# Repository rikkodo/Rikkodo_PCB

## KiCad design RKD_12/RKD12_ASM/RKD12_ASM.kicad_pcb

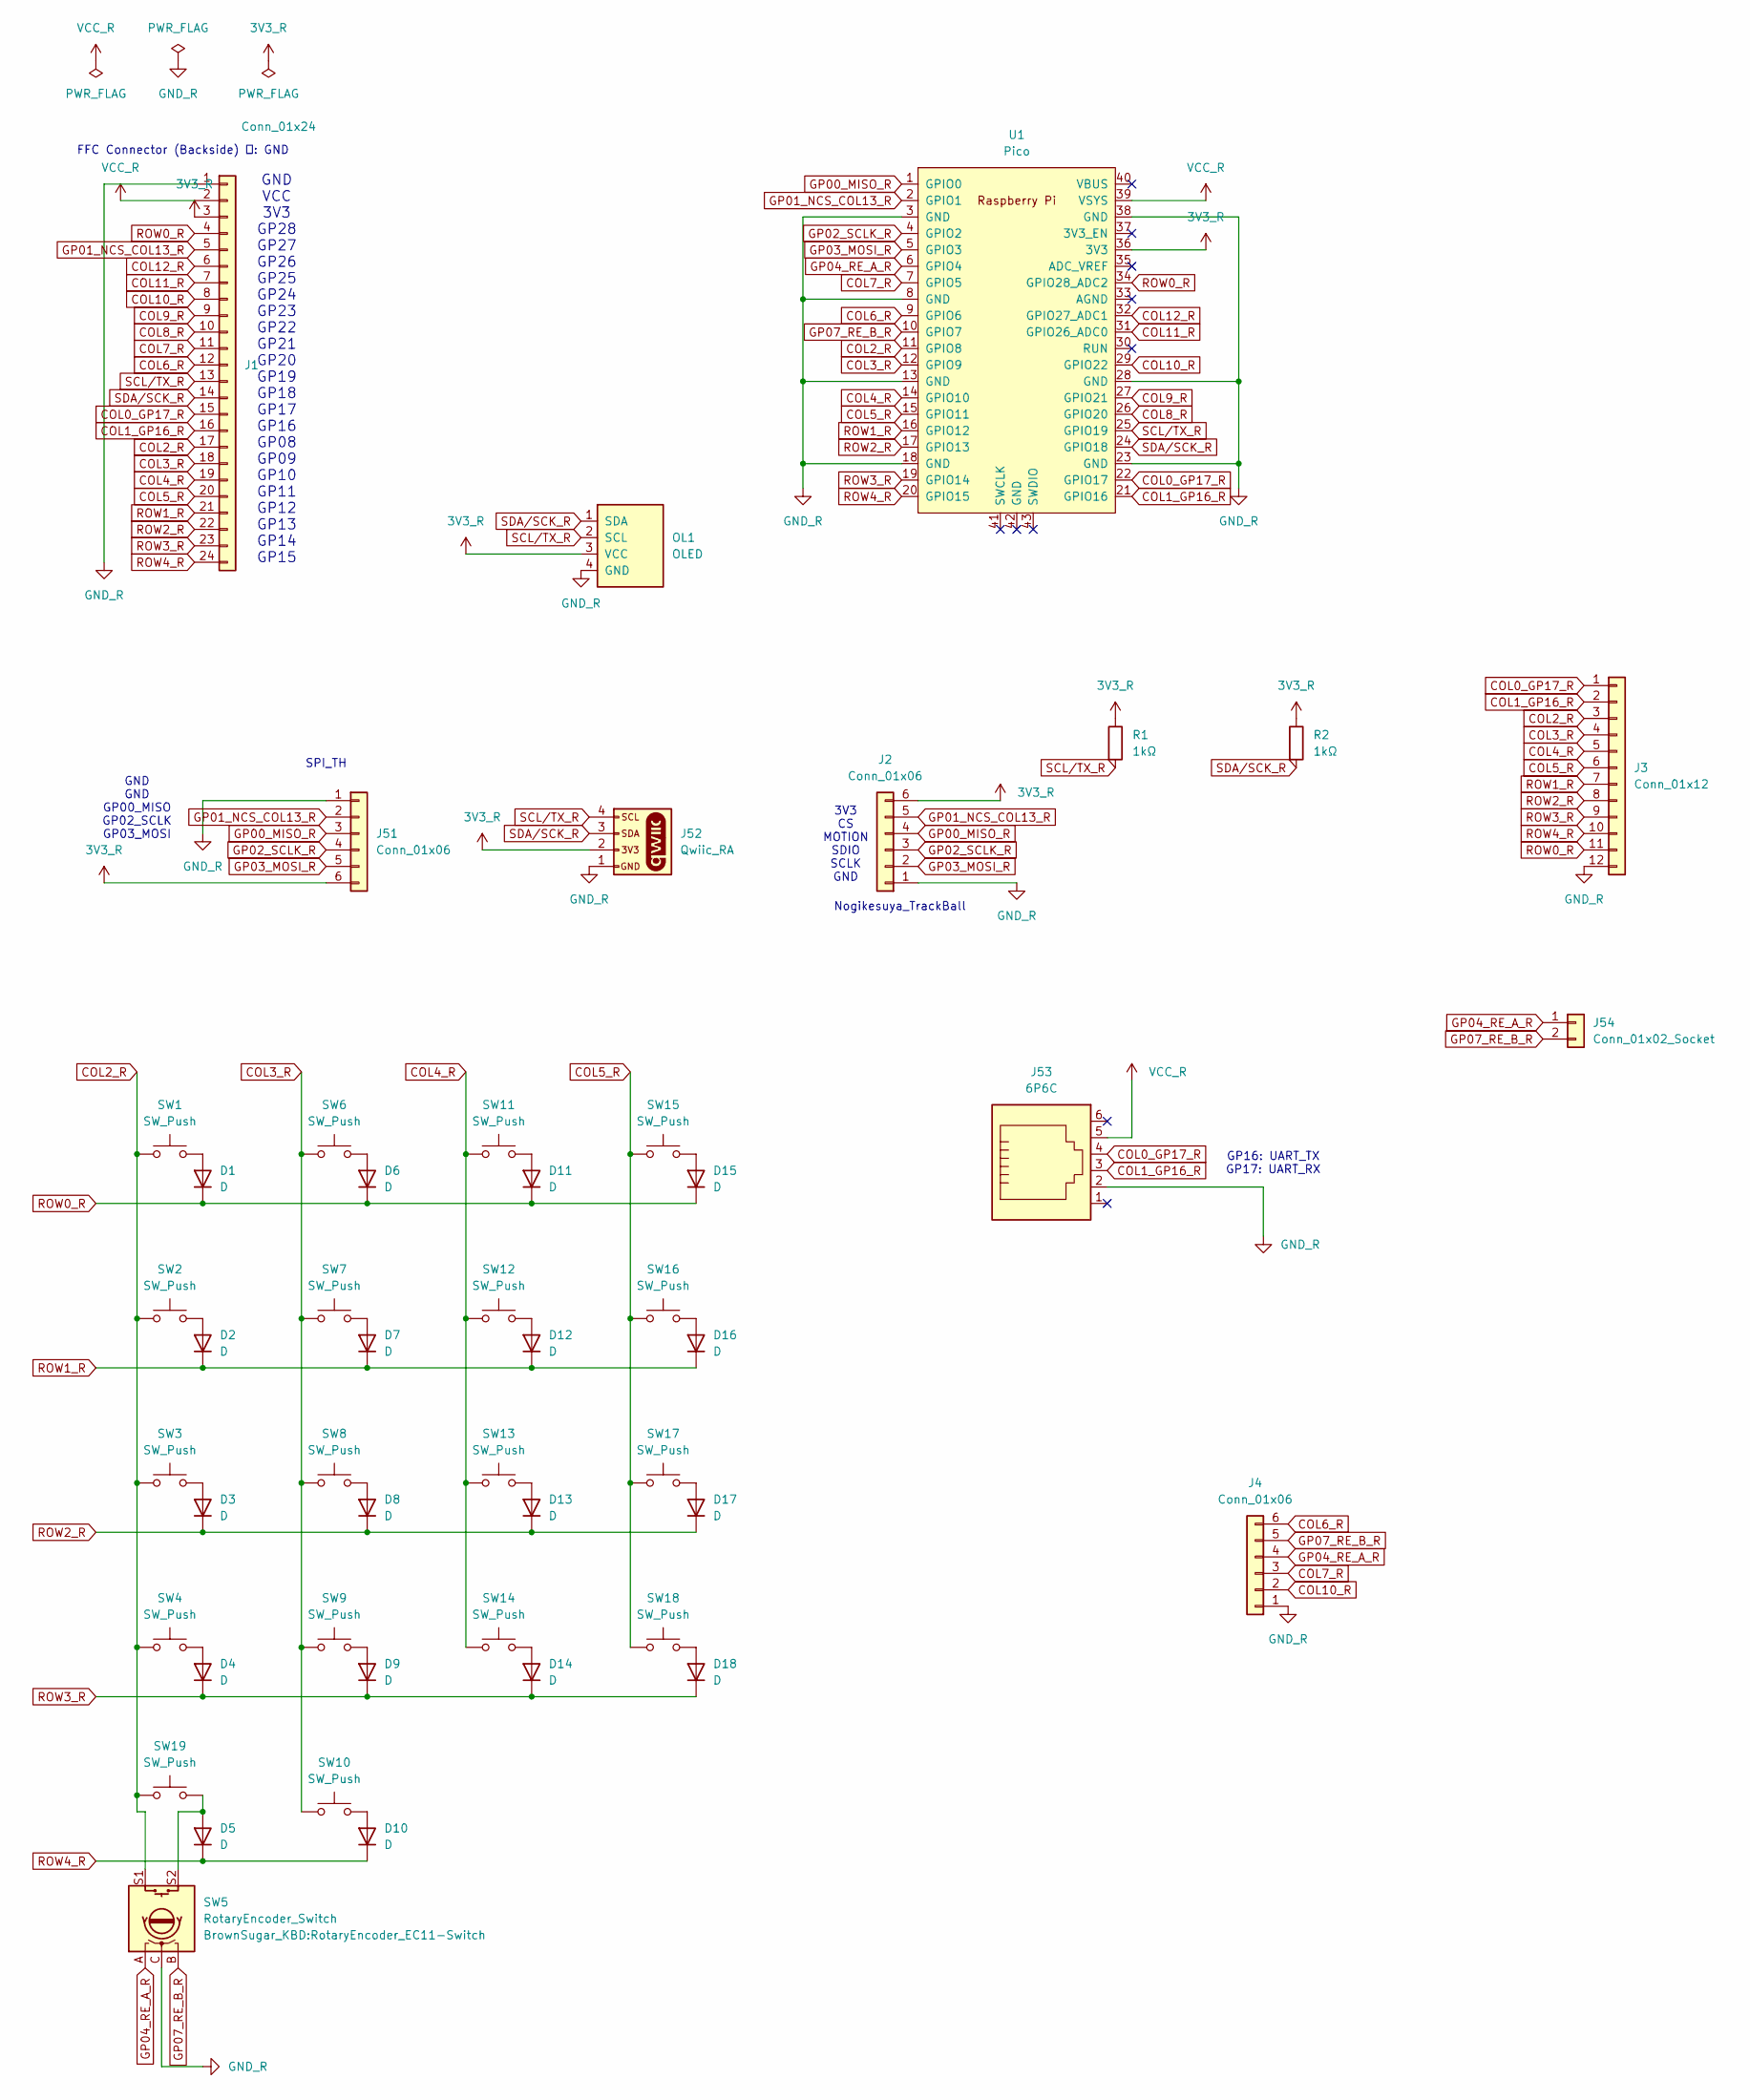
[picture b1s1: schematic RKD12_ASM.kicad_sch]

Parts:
D1, D2, D3, D4, D5, D6, D7, D8, D9, D10, D11, D12, D13, D14, D15, D16, D17, D18: D; Diode_SMD
J1: Conn_01x24; Hirose_FH12-24S-0.5SH_1x24-1MP_P0.50mm_Horizontal
J2, J4: Conn_01x06; Hirose_FH12-6S-0.5SH_1x06-1MP_P0.50mm_Horizontal
J3: Conn_01x12; Hirose_FH12-12S-0.5SH_1x12-1MP_P0.50mm_Horizontal
J51: Conn_01x06; PinHeader_1x06_P2.54mm_Horizontal
J52: Qwiic_RA; JST_SMD_1.0mm-4_Black
J53: 6P6C; RJ12_Amphenol_54601-x06_Horizontal
J54: Conn_01x02_Socket; PinHeader_1x02_P2.54mm_Vertical
OL1: OLED; OLED_center_display
R1, R2: 1kΩ; R_0603_1608Metric
SW1, SW2, SW3, SW4, SW6, SW7, SW8, SW9, SW10, SW11, SW12, SW13, SW14, SW15, SW16, SW17, SW18: SW_Push; rkd_Asm_ChocV1V2_Hotswap_1u_NM
SW5: RotaryEncoder_Switch; RotaryEncoder_EC11-Switch
SW19: SW_Push; ResetSW
U1: Pico; rkd_RPi_Pico_TH_NODBG

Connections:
3V3_R: J1.3, J2.6, J51.6, J52.2, OL1.3 (VCC), R1.1, R2.1, U1.36 (3V3)
COL0_GP17_R: J1.15, J3.1, J53.4, U1.22 (GPIO17)
COL1_GP16_R: J1.16, J3.2, J53.3, U1.21 (GPIO16)
COL2_R: J1.17, J3.3, SW1.2, SW2.2, SW3.2, SW4.2, SW5.S1, SW19.2, U1.11 (GPIO8)
COL3_R: J1.18, J3.4, SW6.2, SW7.2, SW8.2, SW9.2, SW10.2, U1.12 (GPIO9)
COL4_R: J1.19, J3.5, SW11.2, SW12.2, SW13.2, SW14.2, U1.14 (GPIO10)
COL5_R: J1.20, J3.6, SW15.2, SW16.2, SW17.2, SW18.2, U1.15 (GPIO11)
COL6_R: J1.12, J4.6, U1.9 (GPIO6)
COL7_R: J1.11, J4.3, U1.7 (GPIO5)
COL8_R: J1.10, U1.26 (GPIO20)
COL9_R: J1.9, U1.27 (GPIO21)
COL10_R: J1.8, J4.2, U1.29 (GPIO22)
COL11_R: J1.7, U1.31 (GPIO26_ADC0)
COL12_R: J1.6, U1.32 (GPIO27_ADC1)
GND_R: J1.1, J2.1, J3.12, J4.1, J51.1, J52.1, J53.2, OL1.4 (GND), SW5.C, U1.3 (GND), U1.8 (GND), U1.13 (GND), U1.18 (GND), U1.23 (GND), U1.28 (GND), U1.38 (GND)
GP00_MISO_R: J2.4, J51.3, U1.1 (GPIO0)
GP01_NCS_COL13_R: J1.5, J2.5, J51.2, U1.2 (GPIO1)
GP02_SCLK_R: J2.3, J51.4, U1.4 (GPIO2)
GP03_MOSI_R: J2.2, J51.5, U1.5 (GPIO3)
GP04_RE_A_R: J4.4, J54.1, SW5.A, U1.6 (GPIO4)
GP07_RE_B_R: J4.5, J54.2, SW5.B, U1.10 (GPIO7)
unnamed: D1.2 (A), SW1.1
unnamed: D2.2 (A), SW2.1
unnamed: D3.2 (A), SW3.1
unnamed: D4.2 (A), SW4.1
unnamed: D5.2 (A), SW5.S2, SW19.1
unnamed: D6.2 (A), SW6.1
unnamed: D7.2 (A), SW7.1
unnamed: D8.2 (A), SW8.1
unnamed: D9.2 (A), SW9.1
unnamed: D10.2 (A), SW10.1
unnamed: D11.2 (A), SW11.1
unnamed: D12.2 (A), SW12.1
unnamed: D13.2 (A), SW13.1
unnamed: D14.2 (A), SW14.1
unnamed: D15.2 (A), SW15.1
unnamed: D16.2 (A), SW16.1
unnamed: D17.2 (A), SW17.1
unnamed: D18.2 (A), SW18.1
ROW0_R: D1.1 (K), D6.1 (K), D11.1 (K), D15.1 (K), J1.4, J3.11, U1.34 (GPIO28_ADC2)
ROW1_R: D2.1 (K), D7.1 (K), D12.1 (K), D16.1 (K), J1.21, J3.7, U1.16 (GPIO12)
ROW2_R: D3.1 (K), D8.1 (K), D13.1 (K), D17.1 (K), J1.22, J3.8, U1.17 (GPIO13)
ROW3_R: D4.1 (K), D9.1 (K), D14.1 (K), D18.1 (K), J1.23, J3.9, U1.19 (GPIO14)
ROW4_R: D5.1 (K), D10.1 (K), J1.24, J3.10, U1.20 (GPIO15)
SCL/TX_R: J1.13, J52.4, OL1.2 (SCL), R1.2, U1.25 (GPIO19)
SDA/SCK_R: J1.14, J52.3, OL1.1 (SDA), R2.2, U1.24 (GPIO18)
VCC_R: J1.2, J53.5, U1.39 (VSYS)

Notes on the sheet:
Nogikesuya_TrackBall
3V3 CS MOTION SDIO SCLK GND
GND GND GP00_MISO GP02_SCLK GP03_MOSI
SPI_TH
GP16: UART_TX GP17: UART_RX
FFC Connector (Backside) １: GND
GND VCC 3V3 GP28 GP27 GP26 GP25 GP24 GP23 GP22 GP21 GP20 GP19 GP18 GP17 GP16 GP08 GP09 GP10 GP11 GP12 GP13 GP14 GP15

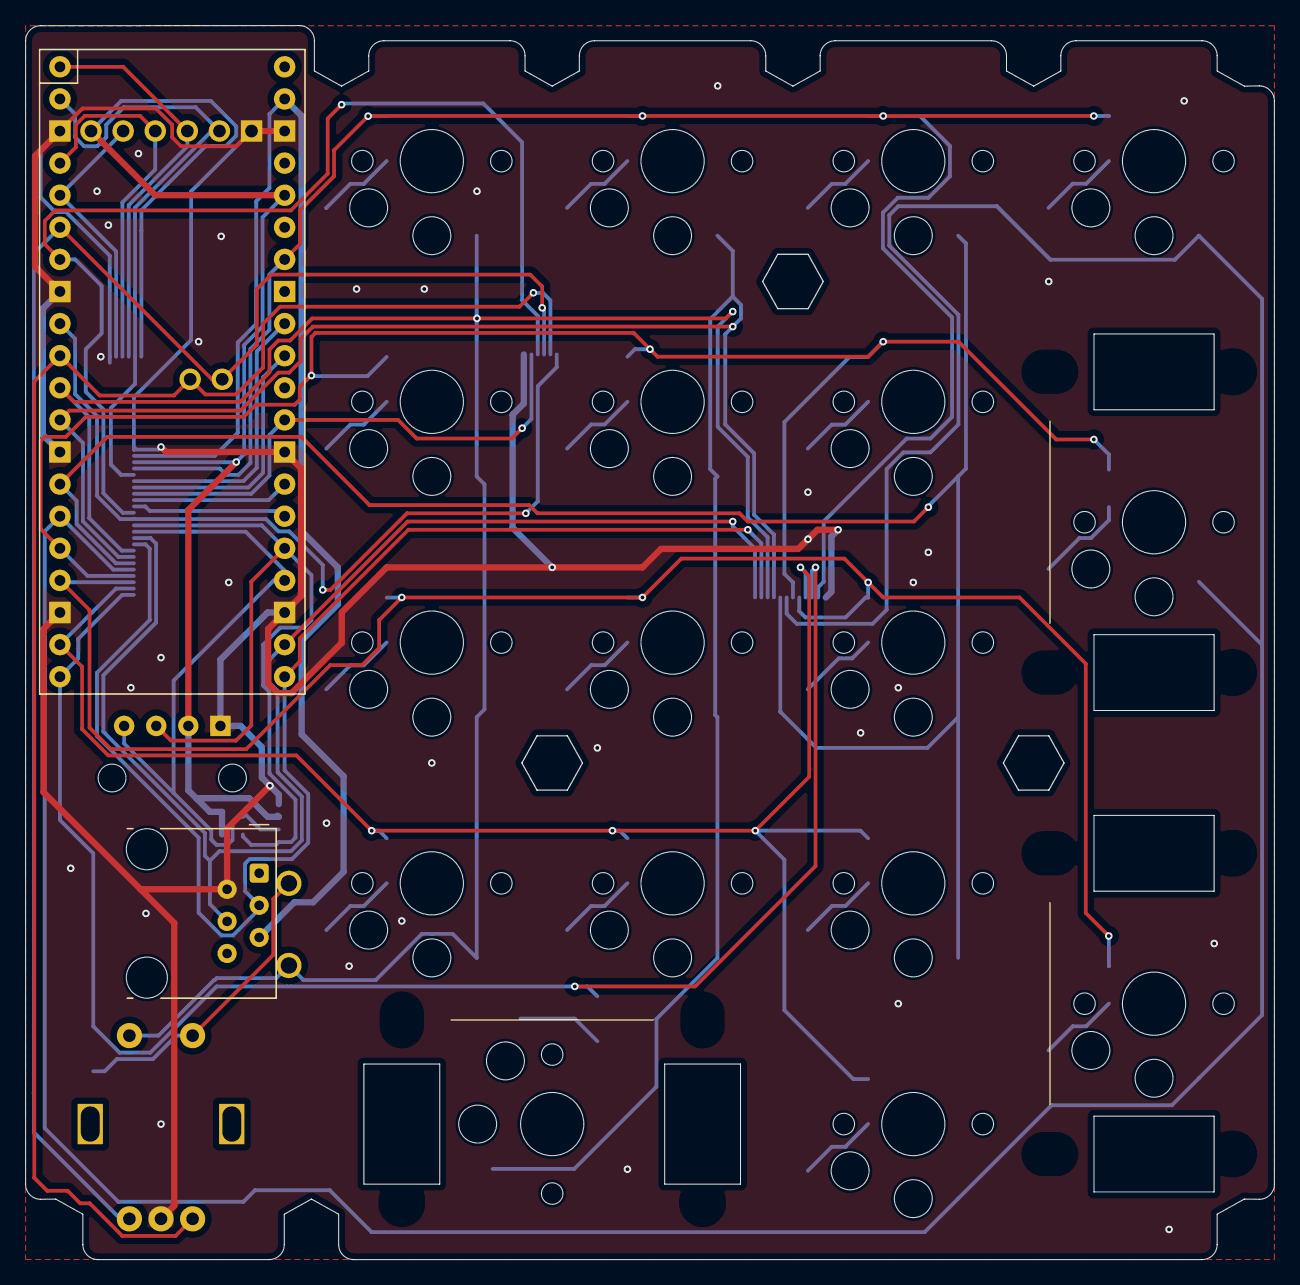
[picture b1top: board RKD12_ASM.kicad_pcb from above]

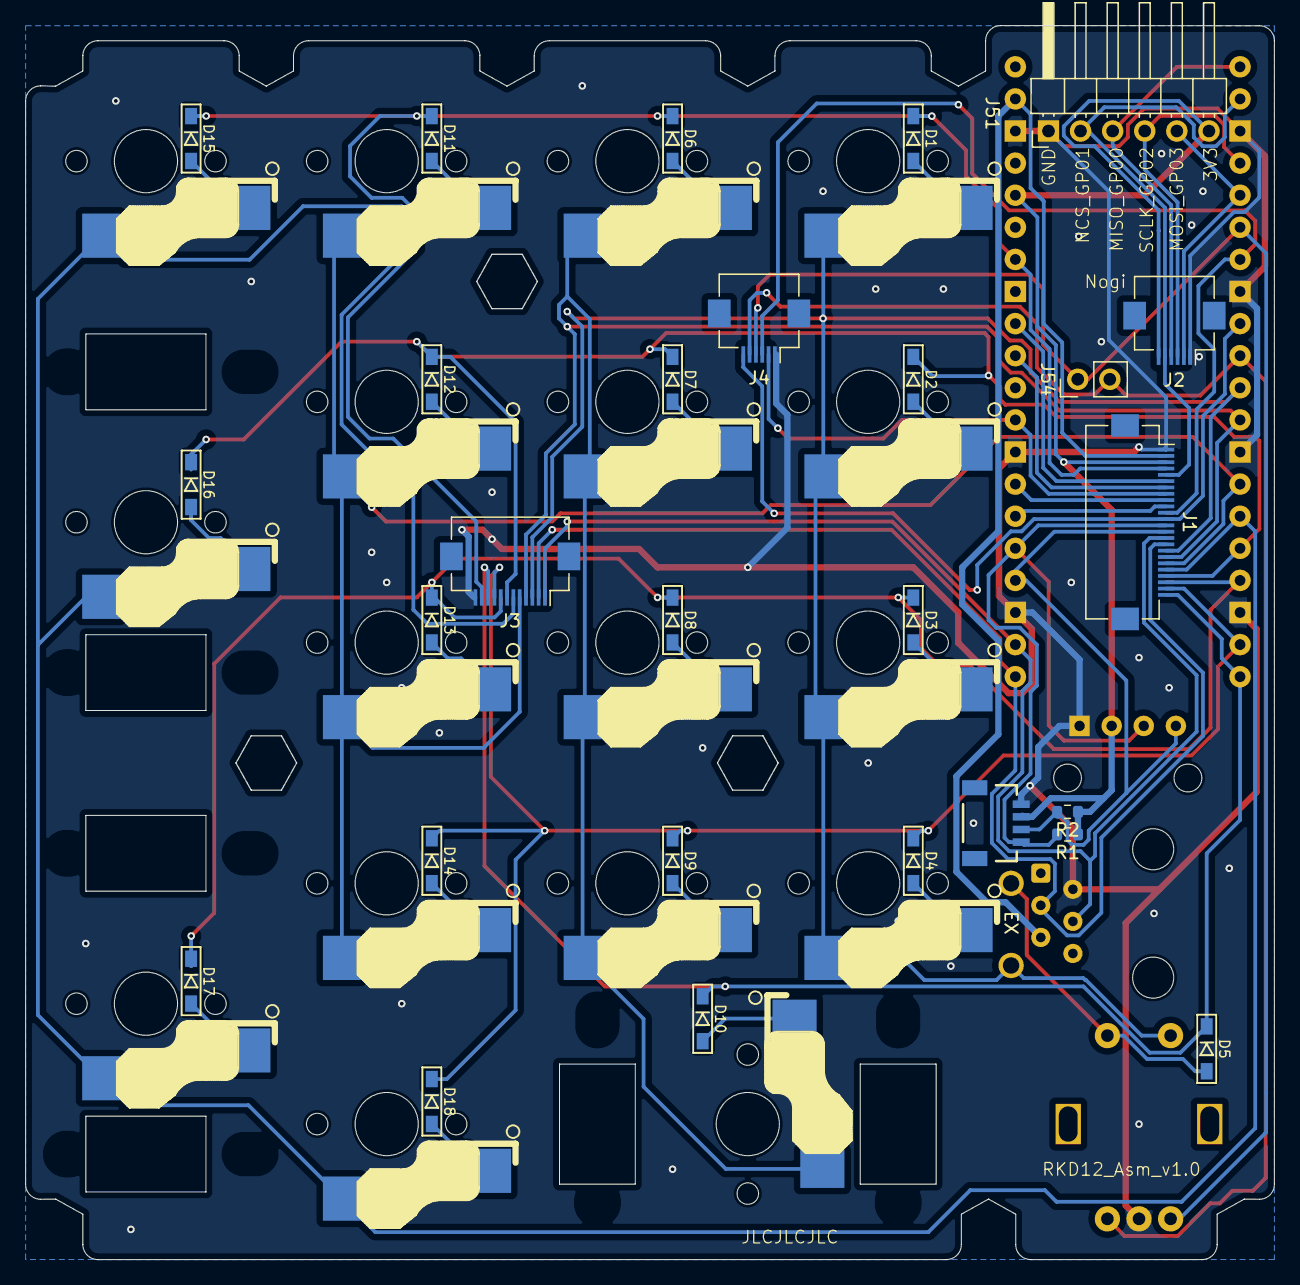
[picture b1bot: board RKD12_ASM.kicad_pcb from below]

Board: 2 copper layers, 98.8 x 97.7 mm, 56 parts (9 on the bottom side), 47 nets.

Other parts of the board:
Point1: Guard_Screw_Hall; rkd_Guard_Screw_Hall
Ref**: Val**; m2_Spacer_Hole_hex
Ref**#2, Ref**#3: Val**; m2_Spacer_Hole_hex
SW99, SW99#2, SW99#3: KEY_SWITCH; rkd_Asm_ChocV2_PCBMountStab_2uL

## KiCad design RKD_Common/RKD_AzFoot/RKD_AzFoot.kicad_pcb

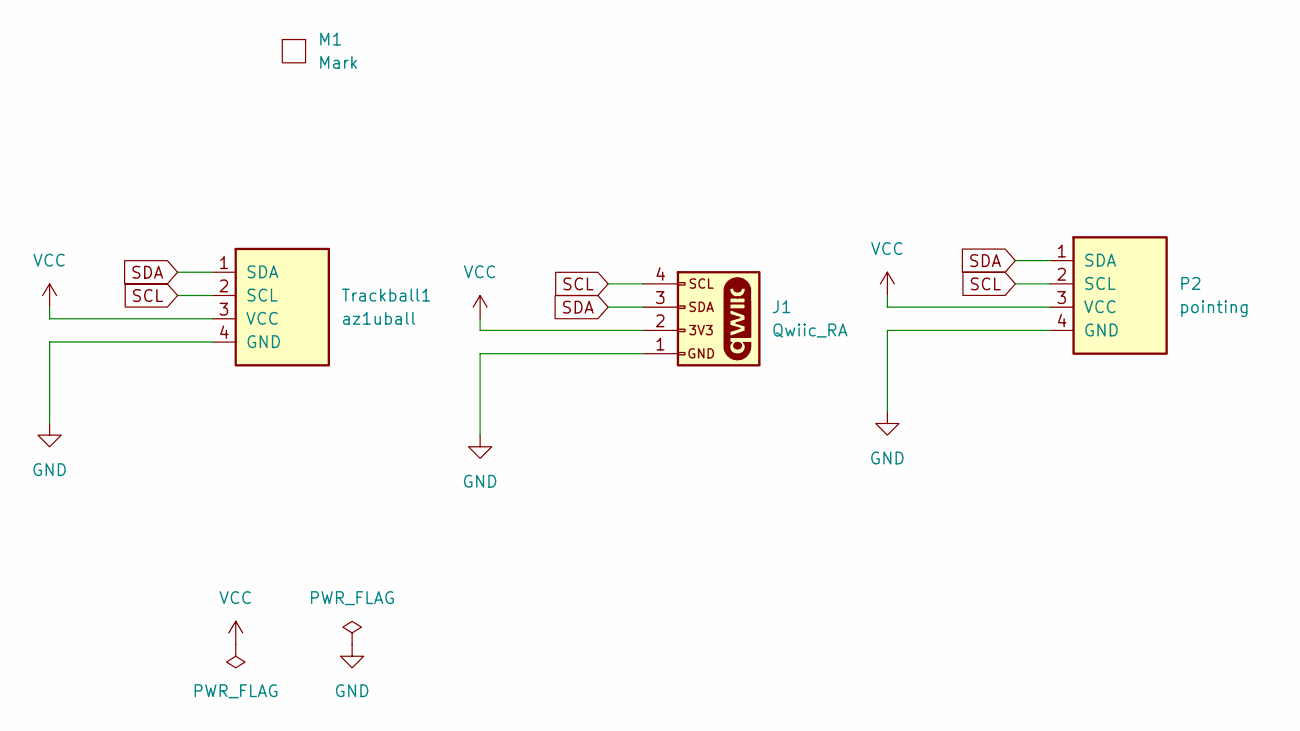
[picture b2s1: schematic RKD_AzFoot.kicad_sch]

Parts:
J1: Qwiic_RA; JST_SMD_1.0mm-4_Black
M1: Mark; rkd_Point_Cut
P2: pointing; OLED
Trackball1: az1uball; AZ1UBALL

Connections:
GND: J1.1, P2.4 (GND), Trackball1.4 (GND)
SCL: J1.4, P2.2 (SCL), Trackball1.2 (SCL)
SDA: J1.3, P2.1 (SDA), Trackball1.1 (SDA)
VCC: J1.2, P2.3 (VCC), Trackball1.3 (VCC)

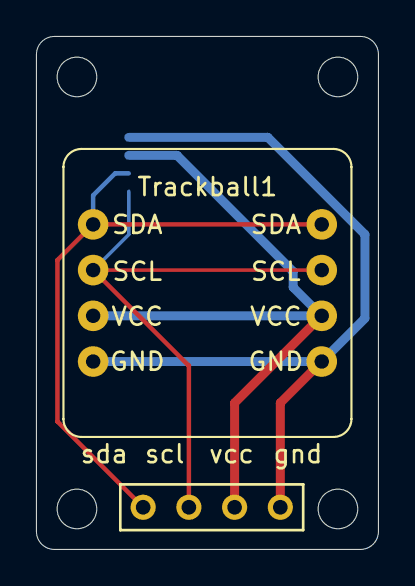
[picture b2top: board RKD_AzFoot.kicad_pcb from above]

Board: 2 copper layers, 19.0 x 28.5 mm, 4 parts (1 on the bottom side), 4 nets.

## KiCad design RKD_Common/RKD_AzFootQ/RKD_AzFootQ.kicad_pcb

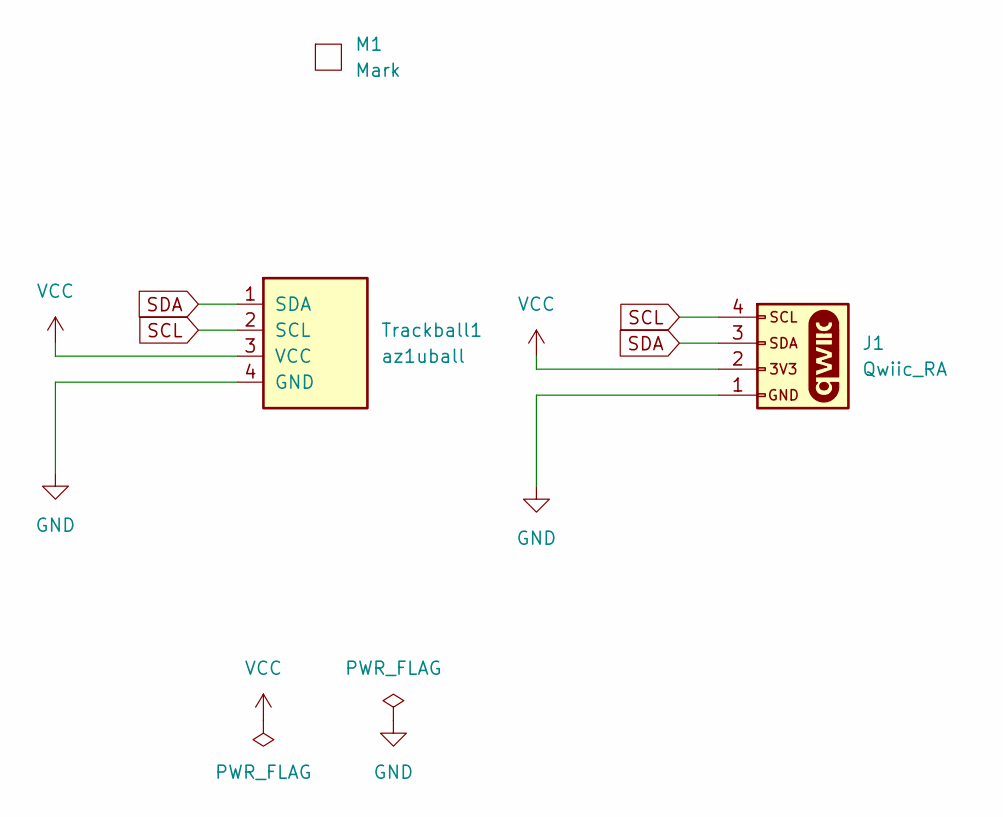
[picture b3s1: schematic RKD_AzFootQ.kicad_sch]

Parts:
J1: Qwiic_RA; JST_SMD_1.0mm-4_Black
M1: Mark; rkd_Point_Cut
Trackball1: az1uball; AZ1UBALL

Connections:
GND: J1.1, Trackball1.4 (GND)
SCL: J1.4, Trackball1.2 (SCL)
SDA: J1.3, Trackball1.1 (SDA)
VCC: J1.2, Trackball1.3 (VCC)

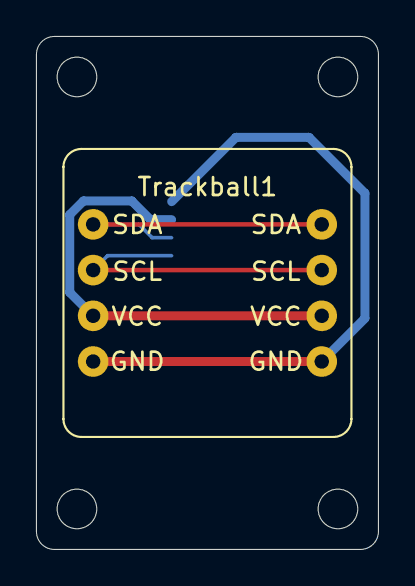
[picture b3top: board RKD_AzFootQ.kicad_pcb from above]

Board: 2 copper layers, 19.0 x 28.5 mm, 3 parts (1 on the bottom side), 4 nets.
